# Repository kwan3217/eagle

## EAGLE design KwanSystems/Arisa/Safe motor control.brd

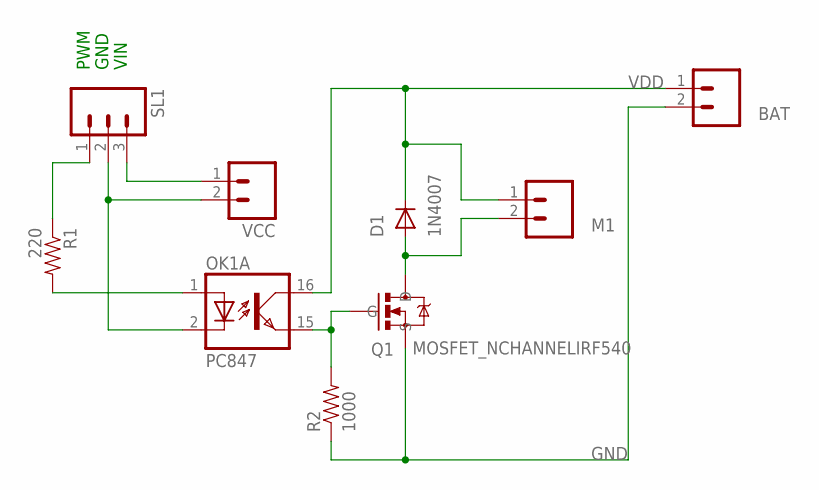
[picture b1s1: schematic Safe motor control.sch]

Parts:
BAT: M025MM; SCREWTERMINAL-5MM-2
D1: 1N4007; DIODE-1N4001
M1: M025MM; SCREWTERMINAL-5MM-2
OK1: PC847; DIL16
Q1: MOSFET_NCHANNELIRF540; TO-220
R1: 220; AXIAL-0.3
R2: 1000; AXIAL-0.3
SL1: M03; 03P
VCC: M02PTH; 1X02

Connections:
GND: BAT.2, Q1.S, R2.P$1 (1)
IN1: R1.P$1 (1)
M1-: D1.A, M1.2, Q1.D
unnamed: OK1.1 (A), R1.P$2 (2)
unnamed: OK1.15 (EMIT), Q1.G, R2.P$2 (2)
unnamed: SL1.3, VCC.1
VDD: BAT.1, D1.C, M1.1, OK1.16 (COL)
VGND: OK1.2 (C), SL1.2, VCC.2

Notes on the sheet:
VIN
GND
PWM

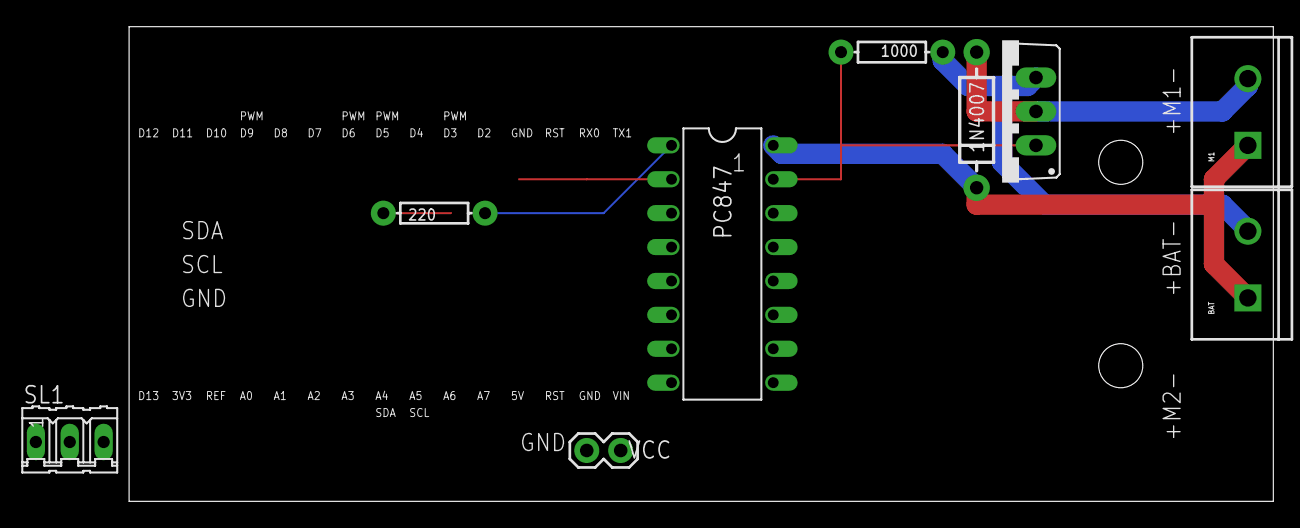
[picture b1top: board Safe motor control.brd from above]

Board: 2 copper layers, 85.7 x 35.6 mm, 12 parts (1 on the bottom side), 7 nets.

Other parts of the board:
U$1, U$2: STAND-OFF
U$3: KWAN_CIRCLE

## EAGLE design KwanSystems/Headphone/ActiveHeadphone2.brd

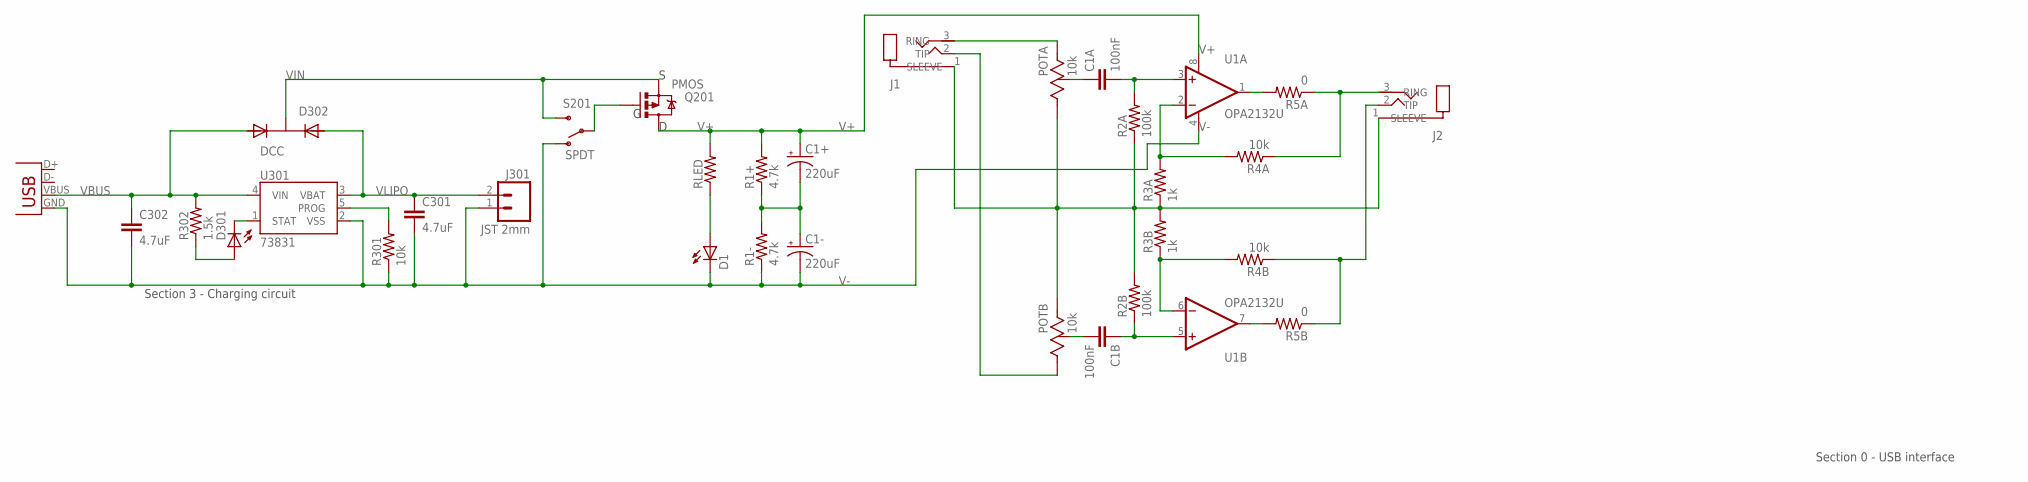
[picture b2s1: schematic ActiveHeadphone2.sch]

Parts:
C1+, C1-: 220uF; EIA7343; DIGIKEY 399-5124-1-ND
C1A, C1B: 100nF; 0603-CAP
C301, C302: 4.7uF; 0603-CAP
D1, D301: RED; LED-0603
D302: DCC; SOT-23-3
J1, J2: 3.5mm; SJ1-3513-SMT
J003: USBSMD; USB-MINIB
J301: JST 2mm; JST-2-SMD
POTA: 10k; 3352T
POTB: 10k; 3352T
Q201: PMOS; SOT23-3
R1+, R1-: 4.7k; 0603-RES
R2A, R2B: 100k; 0603-RES
R3A, R3B: 1k; 0603-RES
R4A, R4B, R301: 10k; 0603-RES
R5A, R5B: 0; 0603-RES
R302: 1.5k; 0603-RES
RLED: RESISTOR0603-RES; 0603-RES
S201: SPDT; AYZ0202
U1: OPA2132U; SO08
U301: 73831; SOT23-5

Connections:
unnamed: C1A.2, R2A.2, U1.3 (+IN)
unnamed: D1.A, RLED.1
unnamed: J2.3 (RING), R4A.1, R5A.1
unnamed: J1.3 (RING), POTA.3 (CW)
unnamed: C1A.1, POTA.2 (WIPER)
unnamed: R5A.2, U1.1 (OUT)
unnamed: R3A.2, R4A.2, U1.2 (-IN)
unnamed: J1.2 (TIP), POTB.1 (CCW)
unnamed: C1B.2, POTB.2 (WIPER)
unnamed: C1B.1, R2B.1, U1.5 (+IN)
unnamed: R3B.1, R4B.2, U1.6 (-IN)
unnamed: R5B.2, U1.7 (OUT)
unnamed: J2.2 (TIP), R4B.1, R5B.1
unnamed: R301.2, U301.5 (PROG)
unnamed: C1+.C (-), C1-.A (+), R1+.1, R1-.2
unnamed: Q201.1 (G), S201.2
unnamed: D301.A, R302.1
unnamed: D301.C, U301.1 (STAT)
V+: C1+.A (+), Q201.3 (D), R1+.2, RLED.2, U1.8 (V+)
V-: C1-.C (-), C301.2, C302.2, D1.C, J003.GND, J301.1, R1-.1, R301.1, S201.1 (O), U1.4 (V-), U301.2 (VSS)
VBUS: C302.1, D302.1 (A1), J003.VBUS, R302.2, U301.4 (VIN)
VGND: J1.1 (SLEEVE), J2.1 (SLEEVE), POTA.1 (CCW), POTB.3 (CW), R2A.1, R2B.2, R3A.1, R3B.2
VIN: D302.3 (K), Q201.2 (S), S201.3 (S)
VLIPO: C301.1, D302.2 (A2), J301.2, U301.3 (VBAT)

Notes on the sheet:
Section 3 - Charging circuit
Section 0 - USB interface

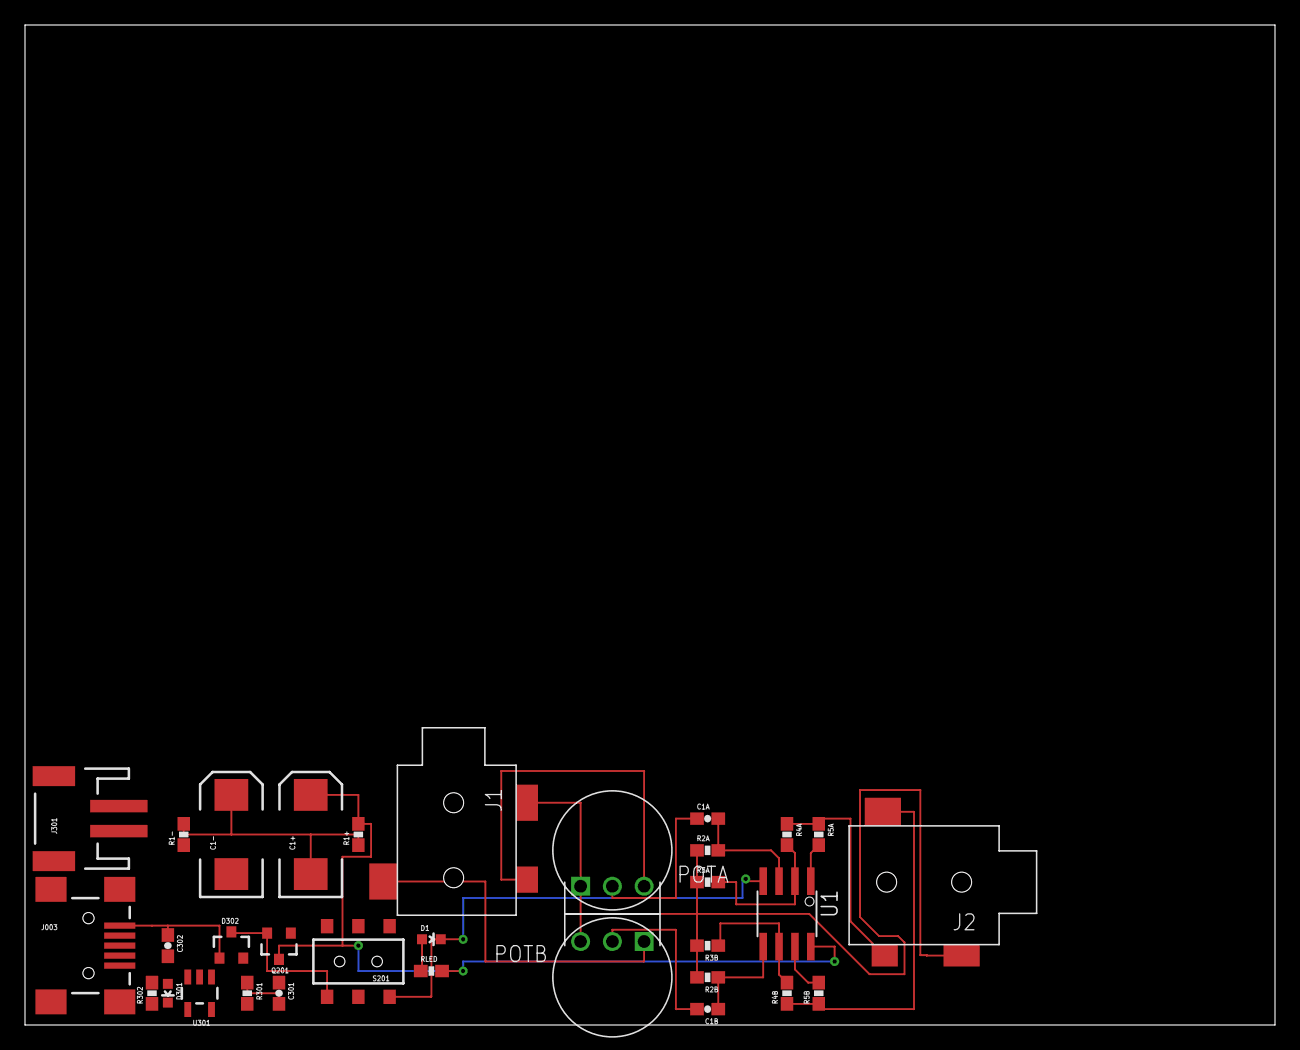
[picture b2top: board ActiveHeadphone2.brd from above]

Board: 2 copper layers, 100.0 x 80.0 mm, 32 parts (0 on the bottom side), 24 nets.

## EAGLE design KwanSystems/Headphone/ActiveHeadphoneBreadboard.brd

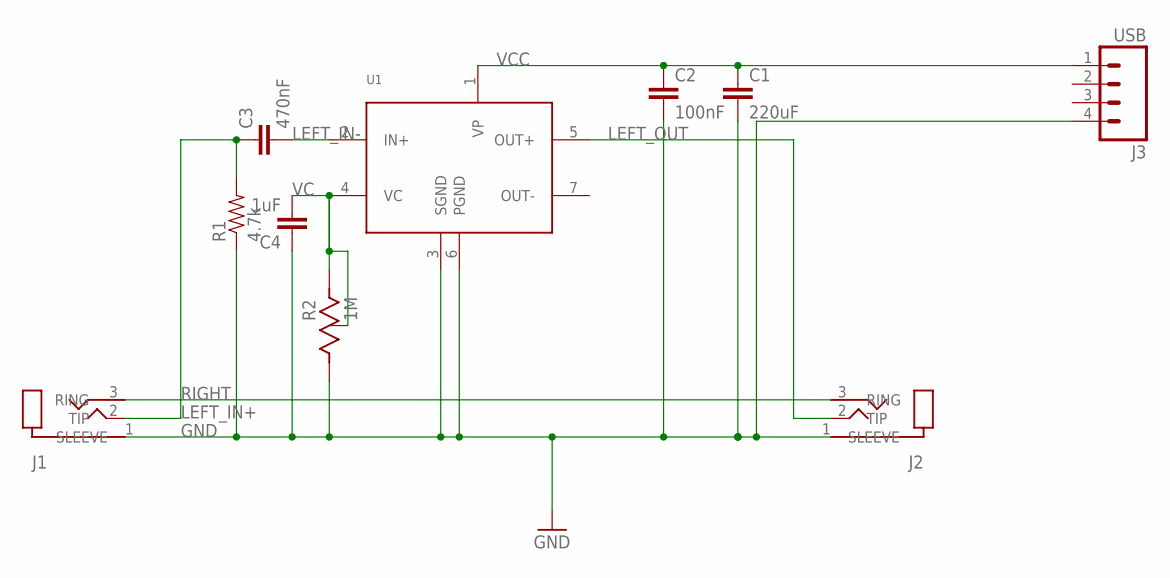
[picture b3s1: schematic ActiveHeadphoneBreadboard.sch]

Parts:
C1: 220uF; CAP-PTH-5MM
C2: 100nF; CAP-PTH-5MM
C3: 470nF; CAP-PTH-SMALL
C4: 1uF; CAP-PTH-SMALL
J1, J2: SJ1-35XXPTH; SJ1-3523N
J3: USB; 1X04
R1: 4.7k; AXIAL-0.4
R2: 1M; 3352T
U1: TDA7052; DIL-8

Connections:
GND: C1.2, C2.2, C4.1, J1.1 (SLEEVE), J2.1 (SLEEVE), J3.4, R1.P$1 (1), R2.1 (CCW), U1.3 (SGND), U1.6 (PGND)
LEFT_IN+: C3.1, J1.2 (TIP), R1.P$2 (2)
LEFT_IN-: C3.2, U1.2 (IN+)
LEFT_OUT: J2.2 (TIP), U1.5 (OUT+)
RIGHT: J1.3 (RING), J2.3 (RING)
VC: C4.2, R2.2 (WIPER), R2.3 (CW), U1.4 (VC)
VCC: C1.1, C2.1, J3.1, U1.1 (VP)

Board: 2 copper layers, 10 parts (0 on the bottom side), 7 nets, no tracks yet.

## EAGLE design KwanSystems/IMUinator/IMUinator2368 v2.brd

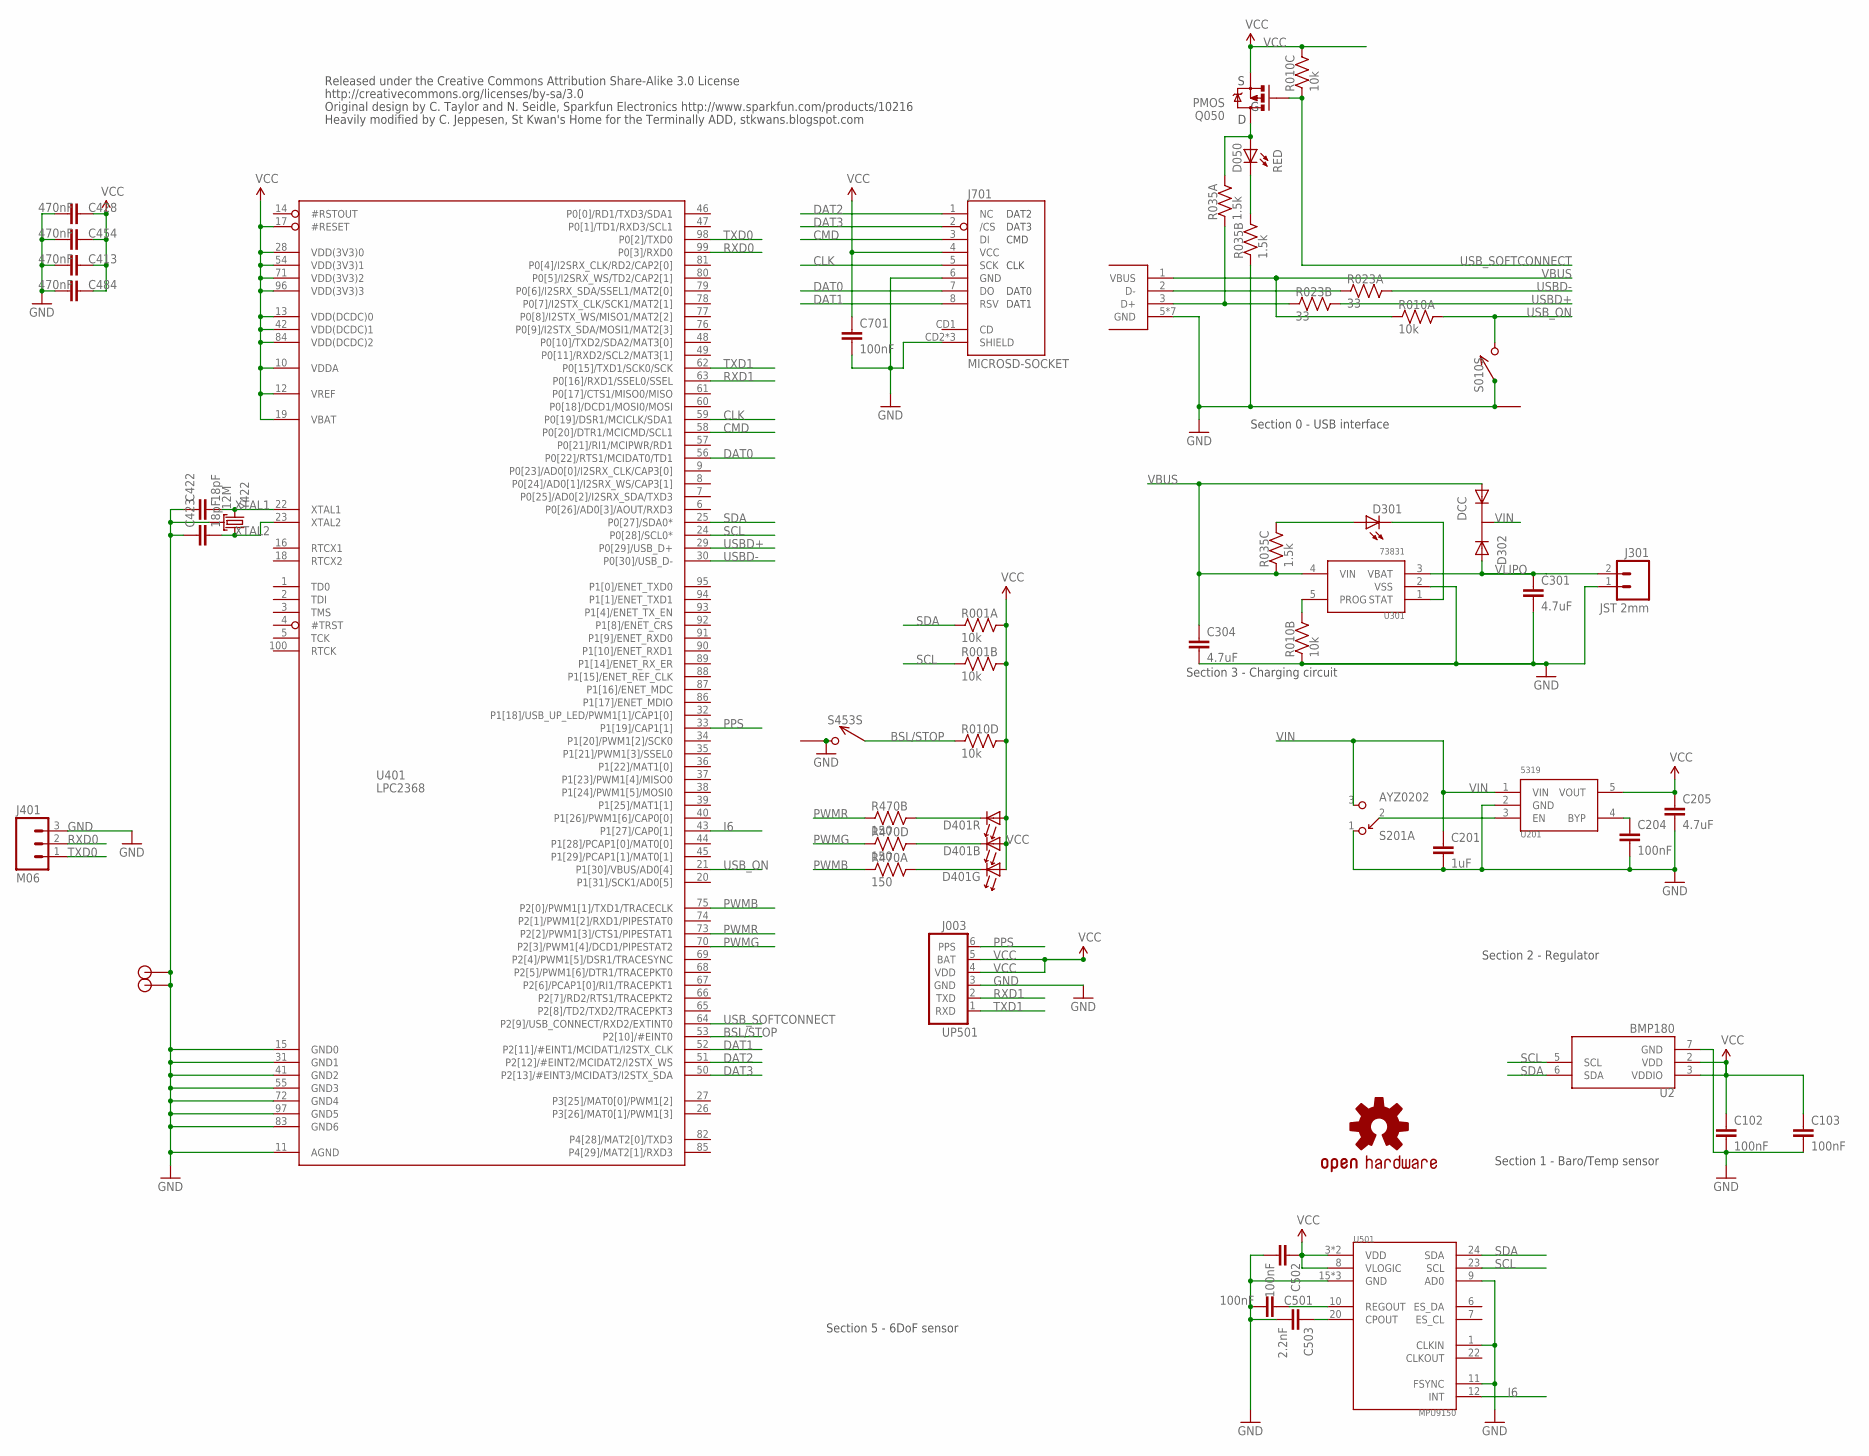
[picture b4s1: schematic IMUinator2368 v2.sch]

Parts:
C102, C103, C204, C501, C502, C701: 100nF; 0402-CAP; DIGIKEY 445-1268-1-ND
C201: 1uF; 0402-CAP; DIGIKEY 445-1415-1-ND
C205, C301, C304: 4.7uF; 0402-CAP; DIGIKEY 445-7395-1-ND
C413: 470nF; 0402-CAP; DIGIKEY 445-4976-1-ND
C422, C423: 18pF; 0402-CAP; DIGIKEY 445-1238-1-ND
C428, C454, C484: 470nF; 0402-CAP; DIGIKEY 445-1268-1-ND
C503: 2.2nF; 0402-CAP; DIGIKEY 445-1268-1-ND
D050, D301: RED; LED-0603; DIGIKEY 350-2029-1-ND
D302: DCC; SOT-23-3; DIGIKEY 568-6500-1-ND
D401: SMLP36RGB2W(R); SMLP36
J001: USB_MICROB_JSTGCT; USB_MICROB_3075; DIGIKEY 455-2562-1-ND
J003: UP501; DIGIKEY $NOPART
J301: JST 2mm; JST-2-SMD; DIGIKEY 455-1749-1-ND
J401: M06; 1X03; DIGIKEY $NOPART
J701: MICROSD-SOCKET; MICROSD-SOCKET-PP; DIGIKEY 101-00581-59-1-ND
JP1, JP2: STANDOFF; DIGIKEY $NOPART
Q050: PMOS; SOT23-3; DIGIKEY NTR1P02T1GOSCT-ND
R001: 10k; CRA02
R010: 10k; CRA04
R023: 33; CRA02
R035: 1.5k; CRA04
R470: 150; CRA04
S010, S453: SPST; B3U-1100P; DIGIKEY SW1021CT-ND
S201: AYZ0202
U2: BMP180; DIGIKEY 828-1027-1-ND
U201: 5319; SOT-23-5; DIGIKEY 576-1910-1-ND
U301: 73831; SOT-23-5; DIGIKEY MCP73831T-2ACI/OTCT-ND
U401: LPC2368; LQFP100; DIGIKEY 568-3997-ND
U501: MPU9150; LLGA24
U$3: OSHW-LOGOS; OSHW-LOGO-S; DIGIKEY $NOPART
Y422: 12M; CRYSTAL_SMD_2MM_2_5MM; DIGIKEY 887-1316-1-ND

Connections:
BSL/STOP: R010.4 (1), S453.P$1 (1), U401.53 (P2[10]/#EINT0)
CLK: J701.5 (SCK), U401.59 (P0[19]/DSR1/MCICLK/SDA1)
CMD: J701.3 (DI), U401.58 (P0[20]/DTR1/MCICMD/SCL1)
CONN_D+: J001.3 (D+), R023.2 (1), R035.1
CONN_D-: J001.2 (D-), R023.1
DAT0: J701.7 (DO), U401.56 (P0[22]/RTS1/MCIDAT0/TD1)
DAT1: J701.8 (RSV), U401.52 (P2[11]/#EINT1/MCIDAT1/I2STX_CLK)
DAT2: J701.1 (NC), U401.51 (P2[12]/#EINT2/MCIDAT2/I2STX_WS)
DAT3: J701.2 (/CS), U401.50 (P2[13]/#EINT3/MCIDAT3/I2STX_SDA)
DB: D401.5 (C), R470.8 (2)
DG: D401.3 (C), R470.7 (2)
GND: C102.2, C103.2, C201.2, C204.2, C205.2, C301.2, C304.2, C413.2, C422.1, C423.1, C428.2, C454.2, C484.2, C501.2, C502.2, C503.2, C701.2, J001.5 (GND), J001.P$1 (GND), J001.P$2 (GND), J001.P$3 (GND), J001.P$4 (GND), J001.P$8 (GND), J001.P$10 (GND), J003.3 (GND), J301.1, J401.3, J701.6 (GND), J701.CD2 (SHIELD), J701.GND1 (SHIELD), J701.GND3 (SHIELD), JP1.P$1, JP2.P$1, R010.2 (1), R035.2 (1), S010.P$1 (1), S010.P$3 (1), S201.1, S453.P$2 (2), S453.P$3 (1), U2.7 (GND), U201.2 (GND), U301.2 (VSS), U401.11 (AGND), U401.15 (GND0), U401.31 (GND1), U401.41 (GND2), U401.55 (GND3), U401.72 (GND4), U401.83 (GND6), U401.97 (GND5), U501.1 (CLKIN), U501.9 (AD0), U501.11 (FSYNC), U501.15 (GND), U501.17 (GND), U501.18 (GND), Y422.2 (GND), Y422.4 (GND)
I6: U401.43 (P1[27]/CAP0[1]), U501.12 (INT)
unnamed: D301.A, R035.6 (2)
unnamed: C503.1, U501.20 (CPOUT)
unnamed: D401.1 (C), R470.5 (2)
unnamed: C501.1, U501.10 (REGOUT)
unnamed: D050.A, Q050.3 (D), R035.8 (2)
unnamed: D050.C, R035.7 (2)
unnamed: C204.1, U201.4 (BYP)
PPS: J003.6 (PPS), U401.33 (P1[19]/CAP1[1])
PWMB: R470.1, U401.75 (P2[0]/PWM1[1]/TXD1/TRACECLK)
PWMG: R470.4 (1), U401.70 (P2[3]/PWM1[4]/DCD1/PIPESTAT2)
PWMR: R470.2 (1), U401.73 (P2[2]/PWM1[3]/CTS1/PIPESTAT1)
PWR_SWITCH: S201.2, U201.3 (EN)
REG_PROG: R010.7 (2), U301.5 (PROG)
REG_STAT: D301.C, U301.1 (STAT)
RXD0: J401.2, U401.99 (P0[3]/RXD0)
RXD1: J003.2 (TXD), U401.63 (P0[16]/RXD1/SSEL0/SSEL)
SCL: R001.2 (1), U2.5 (SCL), U401.24 (P0[28]/SCL0*), U501.23 (SCL)
SDA: R001.1, U2.6 (SDA), U401.25 (P0[27]/SDA0*), U501.24 (SDA)
TXD0: J401.1, U401.98 (P0[2]/TXD0)
TXD1: J003.1 (RXD), U401.62 (P0[15]/TXD1/SCK0/SCK)
USBD+: R023.3 (2), U401.29 (P0[29]/USB_D+)
USBD-: R023.4 (2), U401.30 (P0[30]/USB_D-)
USB_ON: R010.8 (2), S010.P$2 (2), U401.21 (P1[30]/VBUS/AD0[4])
USB_SOFTCONNECT: Q050.1 (G), R010.3 (1), U401.64 (P2[9]/USB_CONNECT/RXD2/EXTINT0)
VBUS: C304.1, D302.1 (A1), J001.1 (VBUS), R010.1, R035.3 (1), U301.4 (VIN)
VCC: C102.1, C103.1, C205.1, C413.1, C428.1, C454.1, C484.1, C502.1, C701.1, D401.2 (A), D401.4 (A), D401.6 (A), J003.4 (VDD), J003.5 (BAT), J701.4 (VCC), Q050.2 (S), R001.3 (2), R001.4 (2), R010.5 (2), R010.6 (2), U2.2 (VDD), U2.3 (VDDIO), U201.5 (VOUT), U401.10 (VDDA), U401.12 (VREF), U401.13 (VDD(DCDC)0), U401.17 (#RESET), U401.19 (VBAT), U401.28 (VDD(3V3)0), U401.42 (VDD(DCDC)1), U401.54 (VDD(3V3)1), U401.71 (VDD(3V3)2), U401.84 (VDD(DCDC)2), U401.96 (VDD(3V3)3), U501.3 (VDD), U501.8 (VLOGIC), U501.13 (VDD)
VIN: C201.1, D302.3 (K), S201.3, U201.1 (VIN)
VLIPO: C301.1, D302.2 (A2), J301.2, U301.3 (VBAT)
XTAL1: C422.2, U401.22 (XTAL1), Y422.3 (2)
XTAL2: C423.2, U401.23 (XTAL2), Y422.1

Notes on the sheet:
Section 2 - Regulator
Section 3 - Charging circuit
Section 0 - USB interface
Released under the Creative Commons Attribution Share-Alike 3.0 License
http://creativecommons.org/licenses/by-sa/3.0
Original design by C. Taylor and N. Seidle, Sparkfun Electronics http://www.sparkfun.com/products/10216
Heavily modified by C. Jeppesen, St Kwan's Home for the Terminally ADD, stkwans.blogspot.com
Section 5 - 6DoF sensor
Section 1 - Baro/Temp sensor

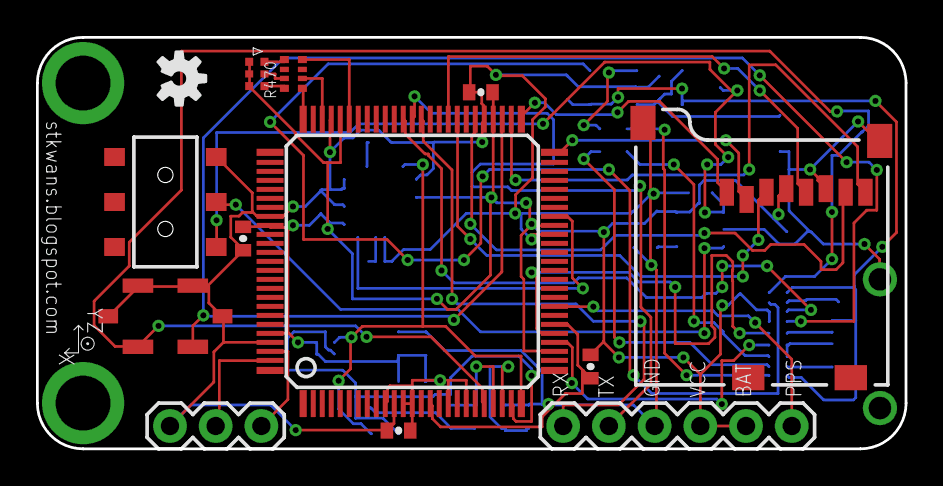
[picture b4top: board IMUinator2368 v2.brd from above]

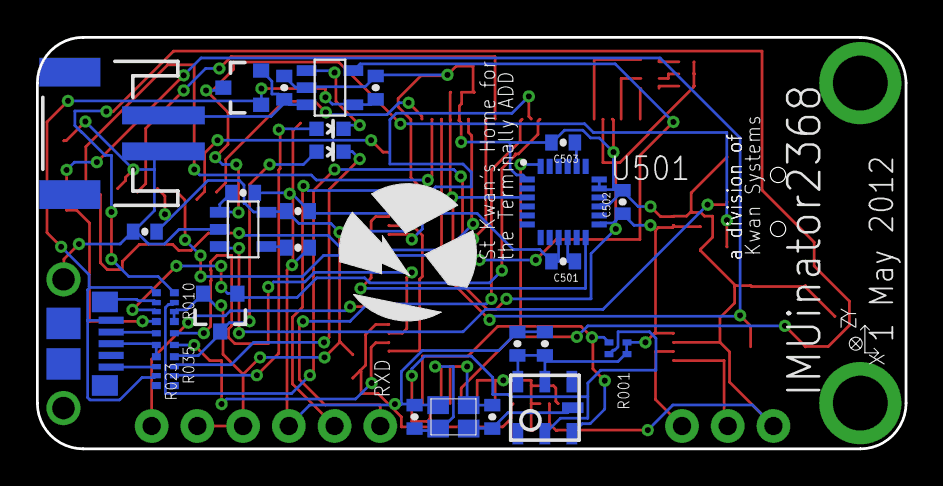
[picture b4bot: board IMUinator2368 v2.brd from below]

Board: 2 copper layers, 48.3 x 22.9 mm, 45 parts (29 on the bottom side), 43 nets.

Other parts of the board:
U$1: KWAN_CIRCLE

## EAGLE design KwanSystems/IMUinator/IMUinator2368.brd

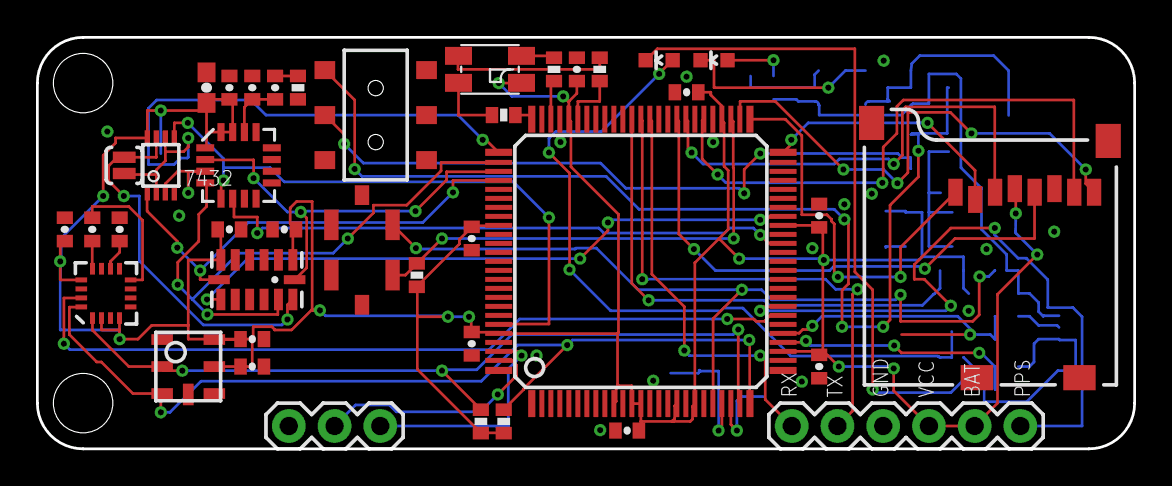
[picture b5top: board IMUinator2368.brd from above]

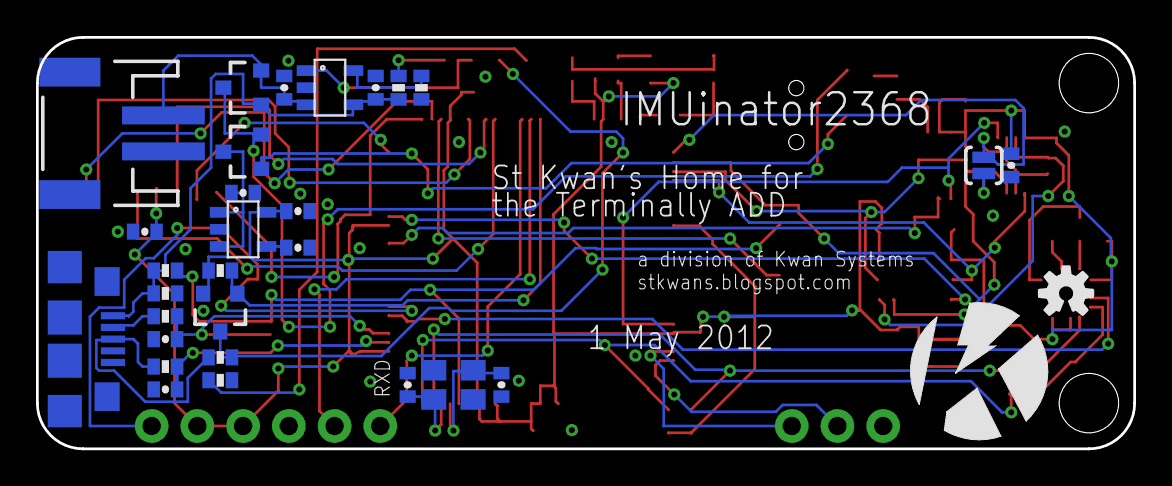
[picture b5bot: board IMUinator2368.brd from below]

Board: 2 copper layers, 61.0 x 22.9 mm, 74 parts (31 on the bottom side), 56 nets.

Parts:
C020, C030, C422, C423: 18pF; 0402-CAP
C102, C103, C204, C401, C428, C442, C454, C471, C484, C496, C501, C601, C701, C802: 100nF; 0402-CAP
C201: 1uF; 0402-CAP
C205, C301, C304, C606, C810: 4.7uF; 0402-CAP
C413, C504: 470nF; 0402-CAP
C502: 10uF; 0603-CAP
C503: 10nF; 0402-CAP
C808: 220nF; 0402-CAP
D050, D301: RED; LED-0603
D302: DCC; SOT-23-3
D401: RGB; HSMF-C118
J001: USB_MICROB_JST; UB-MC5BR3-SD204-4S
J003: UP501
J301: JST 2mm; JST-2-SMD
J401: M06; 1X03
J701: MICROSD-SOCKET; MICROSD-SOCKET-PP
JP1, JP2: STAND-OFF
Q050, Q201: PMOS; SOT23-3
R010, R051, R305, R424, R425, R453, R501: 10k; 0402-RES
R011: 100k; 0402-RES
R020, R030, R470, R475: 33; 0402-RES
R031, R050, R304: 1.5k; 0402-RES
R473: 150; 0402-RES
S010, S453: SPST; B3U-1100P
S201: SPDT; AYZ0202
S501, S601: SOLDERJUMPERNO; SJ_2S-NO
U2: BMP180
U201: 5319; SOT-23-5
U301: 73831; SOT-23-5
U401: LPC2368; LQFP100
U402: 7432; DCU_8
U501: L3G4200D; LGA16-4X4
U601: ADXL345; LGA14
U801: 5883; 16LPCC
U$1: KWAN_CIRCLE
U$3: OSHW-LOGOS; OSHW-LOGO-S
Y422: 12M; CRYSTAL_SMD

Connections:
BSL/STOP: R453.2, S453.P$2, U401.53
CLK: J701.5, U401.59
CMD: J701.3, U401.58
CONN_D+: J001.3, R030.2, R031.2
CONN_D-: J001.2, R020.2
CSA: U401.79, U402.1, U601.7
CSG: U401.95, U402.5, U501.5
DAT0: J701.7, U401.56
DAT1: J701.8, U401.52
DAT2: J701.1, U401.51
DAT3: J701.2, U401.50
DB: D401.4, R475.1
DG: D401.2, R473.1
DR: D401.3, R470.1
GND: C020.2, C030.2, C102.2, C103.2, C201.2, C204.2, C205.2, C301.2, C304.2, C401.2, C413.2, C422.1, C423.1, C428.2, C442.2, C454.2, C471.2, C484.2, C496.2, C501.2, C502.2, C503.2, C601.2, C606.2, C701.2, C802.2, C810.2, J001.5, J001.P$6, J001.P$7, J001.P$8, J001.P$9, J001.P$10, J001.P$11, J003.3, J301.1, J401.3, J701.6, J701.CD2, J701.GND1, J701.GND3, R011.1, R050.2, R305.1, R501.1, S010.P$2, S010.P$3, S201.1, S453.P$1, S453.P$3, U2.7, U201.2, U301.2, U401.11, U401.15, U401.31, U401.41, U401.55, U401.72, U401.83, U401.97, U402.4, U501.8, U501.9, U501.10, U501.11, U501.12, U501.13, U601.2, U601.4, U601.5, U801.9, U801.11, Y422.2, Y422.4
IA: U401.43, U601.8
IC: U401.32, U801.15
IG: U401.40, U501.6
MISO: U401.77, U501.4, U601.12
MOSI: S501.2, S601.2, U401.76, U402.2, U402.6
MOSIA: S601.1, U402.7, U601.13
MOSIG: S501.1, U402.3, U501.3
unnamed: D301.A, R304.1
unnamed: C503.1, C504.1, U501.14
unnamed: C504.2, R501.2
unnamed: D050.A, Q050.3, R031.1
unnamed: D050.C, R050.1
unnamed: C808.1, U801.8
unnamed: C808.2, U801.12
unnamed: C810.1, U801.10
unnamed: C204.1, U201.4
PPS: J003.6, U401.33
PWMB: R475.2, U401.75
PWMG: R470.2, U401.70
PWMR: R473.2, U401.73
PWR_SWITCH: Q201.1, S201.2
RAW: C201.1, Q201.3, U201.1, U201.3
REG_PROG: R305.2, U301.5
REG_STAT: D301.C, U301.1
RXD0: J401.2, U401.99
RXD1: J003.2, U401.63
SCK: U401.78, U501.2, U601.14
SCL: R424.2, U2.5, U401.24, U801.1
SDA: R425.2, U2.6, U401.25, U801.16
TXD0: J401.1, U401.98
TXD1: J003.1, U401.62
USBD+: C030.1, R030.1, U401.29
USBD-: C020.1, R020.1, U401.30
USB_ON: R010.1, S010.P$1, U401.21
USB_SOFTCONNECT: Q050.1, R051.2, U401.64
VBUS: C304.1, D302.1, J001.1, R010.2, R011.2, R304.2, U301.4
VCC: C102.1, C103.1, C205.1, C401.1, C413.1, C428.1, C442.1, C454.1, C471.1, C484.1, C496.1, C501.1, C502.1, C601.1, C606.1, C701.1, C802.1, D401.1, J003.4, J003.5, J701.4, Q050.2, R051.1, R424.1, R425.1, R453.1, U2.2, U2.3, U201.5, U401.10, U401.12, U401.13, U401.17, U401.19, U401.28, U401.42, U401.54, U401.71, U401.84, U401.96, U402.8, U501.1, U501.15, U501.16, U601.1, U601.6, U801.2, U801.4, U801.13
VIN: D302.3, Q201.2, S201.3
VLIPO: C301.1, D302.2, J301.2, U301.3
XTAL1: C422.2, U401.22, Y422.3
XTAL2: C423.2, U401.23, Y422.1

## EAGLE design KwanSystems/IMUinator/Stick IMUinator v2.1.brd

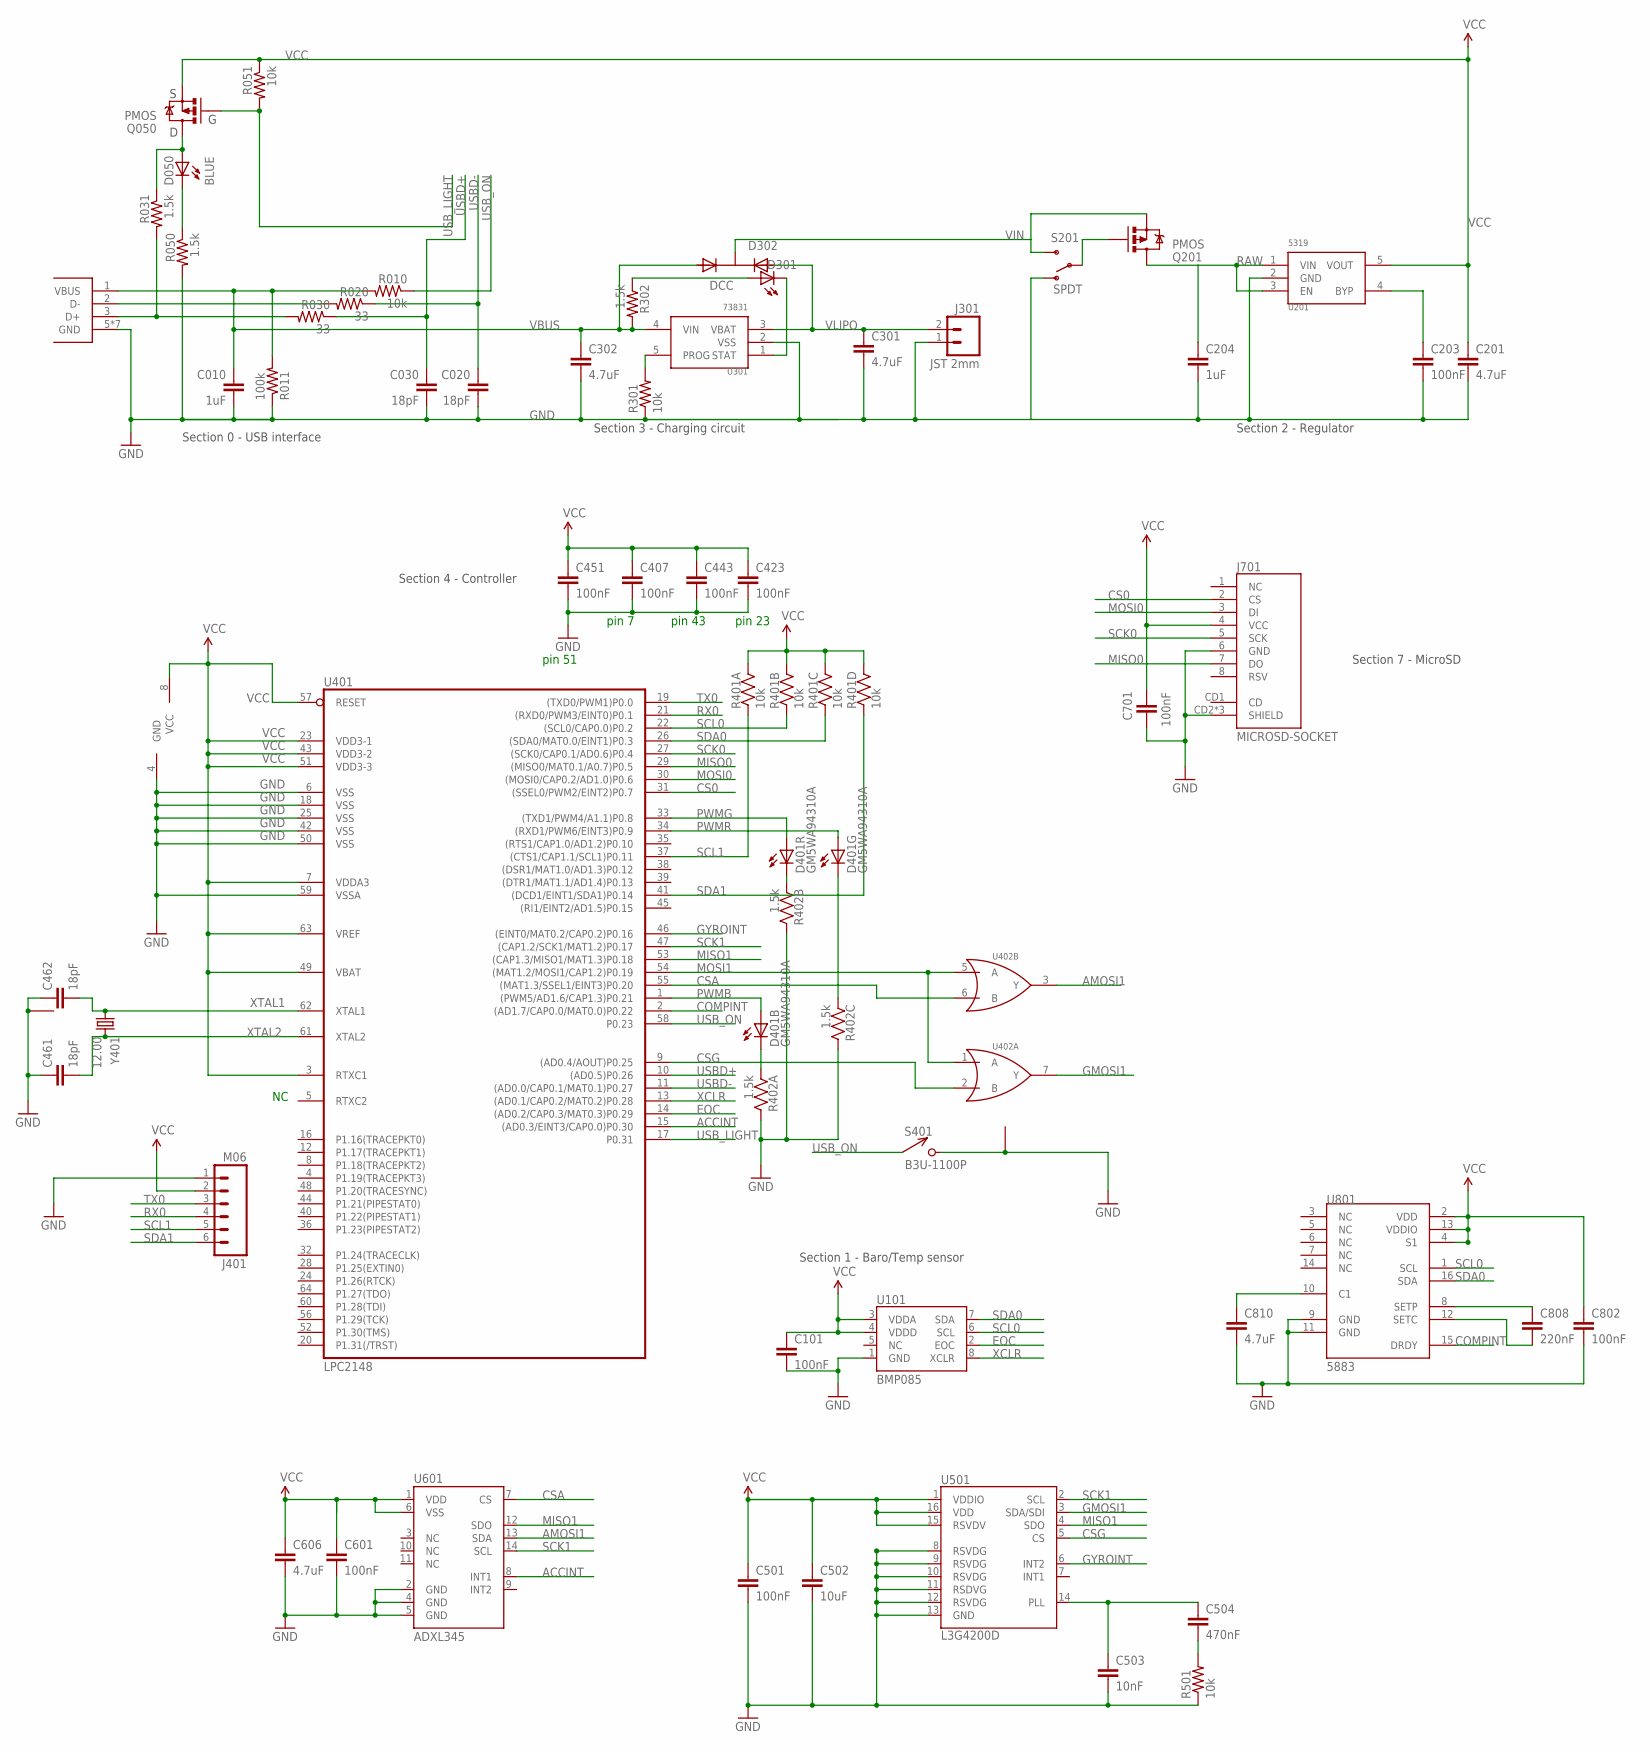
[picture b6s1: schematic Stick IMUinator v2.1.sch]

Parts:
C010, C204: 1uF; 0402-CAP; DIGIKEY 445-1415-1-ND
C020, C030, C461, C462: 18pF; 0402-CAP; DIGIKEY 445-1238-1-ND
C101, C203, C407, C423, C443, C451, C501, C601, C701, C802: 100nF; 0402-CAP; DIGIKEY 445-1268-1-ND
C201, C301, C302, C606, C810: 4.7uF; 0402-CAP; DIGIKEY 445-7395-1-ND
C502: 10uF; 0603-CAP; DIGIKEY 445-7486-1-ND
C503: 10nF; 0402-CAP; DIGIKEY 445-4943-1-ND
C504: 470nF; 0402-CAP; DIGIKEY 445-4976-1-ND
C808: 220nF; 0402-CAP; DIGIKEY 445-4972-1-ND
D050: BLUE; LED-0603; DIGIKEY 350-2029-1-ND
D301: YELLOW; LED-0603; DIGIKEY 350-2029-1-ND
D302: DCC; SOT-23-3; DIGIKEY 568-6500-1-ND
D401: GM5WA94310A; DIGIKEY 425-2728-1-ND
J001: USB_MICROB_JST; UB-MC5BR3-SD204-4S; DIGIKEY 455-2562-1-ND
J301: JST 2mm; JST-2-SMD; DIGIKEY 455-1749-1-ND
J401: M06; 1X06_LOCK; DIGIKEY $NOPART
J701: MICROSD-SOCKET; MICROSD-SOCKET-PP; DIGIKEY 101-00581-59-1-ND
Q050, Q201: PMOS; SOT23-3; DIGIKEY NTR1P02T1GOSCT-ND
R010, R051, R301, R501: 10k; 0402-RES; DIGIKEY P10.0KLCT-ND
R011: 100k; 0402-RES; DIGIKEY P100KLCT-ND
R020, R030: 33; 0402-RES; DIGIKEY P33.0LCT-ND
R031, R050, R302: 1.5k; 0402-RES; DIGIKEY P1.50KLCT-ND
R401: 10k; CRA04; DIGIKEY CRA4S810KCT-ND
R402: 1.5k; CRA04; DIGIKEY CRA4S81.5KCT-ND
S201: SPDT; AYZ0202; DIGIKEY 401-2013-1-ND
S401: B3U-1100P; DIGIKEY SW1021CT-ND
U101: BMP085; DIGIKEY 828-1005-1-ND
U201: 5319; SOT-23-5; DIGIKEY 576-1910-1-ND
U301: 73831; SOT-23-5; DIGIKEY MCP73831T-2ACI/OTCT-ND
U401: LPC2148; SQFP-S-10X10-64; DIGIKEY 568-1765-ND
U402: 7432; DCU_8; DIGIKEY 296-13268-1-ND
U501: L3G4200D; LGA16-4X4; DIGIKEY 497-11071-1-ND
U601: ADXL345; LGA14; DIGIKEY ADXL345BCCZ-RL7CT-ND
U801: 5883; 16LPCC; DIGIKEY 342-1082-1-ND
Y401: 12.00; CRYSTAL_SMD; DIGIKEY 887-1316-1-ND

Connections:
ACCINT: U401.15 ((AD0.3/EINT3/CAP0.0)P0.30), U601.8 (INT1)
AMOSI1: U402.3 (Y), U601.13 (SDA)
COMPINT: U401.2 ((AD1.7/CAP0.0/MAT0.0)P0.22), U801.15 (DRDY)
CONN_D+: J001.3 (D+), R030.2, R031.2
CONN_D-: J001.2 (D-), R020.2
CS0: J701.2 (CS), U401.31 ((SSEL0/PWM2/EINT2)P0.7)
CSA: U401.55 ((MAT1.3/SSEL1/EINT3)P0.20), U402.6 (B), U601.7 (CS)
CSG: U401.9 ((AD0.4/AOUT)P0.25), U402.2 (B), U501.5 (CS)
EOC: U101.2 (EOC), U401.14 ((AD0.2/CAP0.3/MAT0.3)P0.29)
GMOSI1: U402.7 (Y), U501.3 (SDA/SDI)
GND: C010.2, C020.2, C030.2, C101.2, C201.2, C203.2, C204.2, C301.2, C302.2, C407.2, C423.2, C443.2, C451.2, C461.1, C462.1, C501.2, C502.2, C503.2, C601.2, C606.2, C701.2, C802.2, C810.2, J001.5 (GND), J001.P$6 (GND), J001.P$7 (GND), J001.P$8 (GND), J001.P$9 (GND), J001.P$10 (GND), J001.P$11 (GND), J301.1, J401.1, J701.6 (GND), J701.CD2 (SHIELD), J701.GND1 (SHIELD), J701.GND3 (SHIELD), R011.1, R050.2, R301.1, R402.6 (2), R402.7 (2), R402.8 (2), R501.1, S201.1 (O), S401.P$2 (2), S401.P$3 (1), U101.1 (GND), U201.2 (GND), U301.2 (VSS), U401.6 (VSS), U401.18 (VSS), U401.25 (VSS), U401.42 (VSS), U401.50 (VSS), U401.59 (VSSA), U402.4 (GND), U501.8 (RSVDG), U501.9 (RSVDG), U501.10 (RSVDG), U501.11 (RSDVG), U501.12 (RSVDG), U501.13 (GND), U601.2 (GND), U601.4 (GND), U601.5 (GND), U801.9 (GND), U801.11 (GND), Y401.2 (1), Y401.4 (1)
GYROINT: U401.46 ((EINT0/MAT0.2/CAP0.2)P0.16), U501.6 (INT2)
MISO0: J701.7 (DO), U401.29 ((MISO0/MAT0.1/A0.7)P0.5)
MISO1: U401.53 ((CAP1.3/MISO1/MAT1.3)P0.18), U501.4 (SDO), U601.12 (SDO)
MOSI0: J701.3 (DI), U401.30 ((MOSI0/CAP0.2/AD1.0)P0.6)
MOSI1: U401.54 ((MAT1.2/MOSI1/CAP1.2)P0.19), U402.1 (A), U402.5 (A)
unnamed: C504.2, R501.2
unnamed: R301.2, U301.5 (PROG)
unnamed: D401.4 (C), R402.3 (1)
unnamed: D301.C, U301.1 (STAT)
unnamed: D301.A, R302.1
unnamed: D050.A, Q050.3 (D), R031.1
unnamed: D050.C, R050.1
unnamed: D401.5 (C), R402.2 (1)
unnamed: Q201.1 (G), S201.2
unnamed: D401.6 (C), R402.1
unnamed: C808.1, U801.8 (SETP)
unnamed: C808.2, U801.12 (SETC)
unnamed: C810.1, U801.10 (C1)
unnamed: C203.1, U201.4 (BYP)
unnamed: C503.1, C504.1, U501.14 (PLL)
PWMB: D401.1 (A), U401.1 ((PWM5/AD1.6/CAP1.3)P0.21)
PWMG: D401.3 (A), U401.34 ((RXD1/PWM6/EINT3)P0.9)
PWMR: D401.2 (A), U401.33 ((TXD1/PWM4/A1.1)P0.8)
RAW: C204.1, Q201.3 (D), U201.1 (VIN), U201.3 (EN)
RX0: J401.4, U401.21 ((RXD0/PWM3/EINT0)P0.1)
SCK0: J701.5 (SCK), U401.27 ((SCK0/CAP0.1/AD0.6)P0.4)
SCK1: U401.47 ((CAP1.2/SCK1/MAT1.2)P0.17), U501.2 (SCL), U601.14 (SCL)
SCL0: R401.2 (1), U101.6 (SCL), U401.22 ((SCL0/CAP0.0)P0.2), U801.1 (SCL)
SCL1: J401.5, R401.1, U401.37 ((CTS1/CAP1.1/SCL1)P0.11)
SDA0: R401.3 (1), U101.7 (SDA), U401.26 ((SDA0/MAT0.0/EINT1)P0.3), U801.16 (SDA)
SDA1: J401.6, R401.4 (1), U401.41 ((DCD1/EINT1/SDA1)P0.14)
TX0: J401.3, U401.19 ((TXD0/PWM1)P0.0)
USBD+: C030.1, R030.1, U401.10 ((AD0.5)P0.26)
USBD-: C020.1, R020.1, U401.11 ((AD0.0/CAP0.1/MAT0.1)P0.27)
USB_LIGHT: Q050.1 (G), R051.2, U401.17 (P0.31)
USB_ON: R010.1, S401.P$1 (1), U401.58 (P0.23)
VBUS: C010.1, C302.1, D302.1 (A1), J001.1 (VBUS), R010.2, R011.2, R302.2, U301.4 (VIN)
VCC: C101.1, C201.1, C407.1, C423.1, C443.1, C451.1, C501.1, C502.1, C601.1, C606.1, C701.1, C802.1, J401.2, J701.4 (VCC), Q050.2 (S), R051.1, R401.5 (2), R401.6 (2), R401.7 (2), R401.8 (2), U101.3 (VDDA), U101.4 (VDDD), U201.5 (VOUT), U401.3 (RTXC1), U401.7 (VDDA3), U401.23 (VDD3-1), U401.43 (VDD3-2), U401.49 (VBAT), U401.51 (VDD3-3), U401.57 (RESET), U401.63 (VREF), U402.8 (VCC), U501.1 (VDDIO), U501.15 (RSVDV), U501.16 (VDD), U601.1 (VDD), U601.6 (VSS), U801.2 (VDD), U801.4 (S1), U801.13 (VDDIO)
VIN: D302.3 (K), Q201.2 (S), S201.3 (S)
VLIPO: C301.1, D302.2 (A2), J301.2, U301.3 (VBAT)
XCLR: U101.8 (XCLR), U401.13 ((AD0.1/CAP0.2/MAT0.2)P0.28)
XTAL1: C462.2, U401.62 (XTAL1), Y401.1
XTAL2: C461.2, U401.61 (XTAL2), Y401.3 (2)

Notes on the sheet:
Section 2 - Regulator
Section 3 - Charging circuit
Section 0 - USB interface
pin 51
pin 7
pin 43
pin 23
Section 4 - Controller
Section 7 - MicroSD
Section 1 - Baro/Temp sensor

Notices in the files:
parts and their libraries:
SparkFun: Licensing: CC v3.0 Share-Alike You are welcome to use this library for commercial purposes.
